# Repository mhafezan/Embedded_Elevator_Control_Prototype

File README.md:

# Embedded Elevator Control Prototype

A C-based embedded elevator controller prototype that simulates the core logic of a multi-floor elevator system using a finite-state machine. The project includes both a terminal-based simulator and a graphical simulator built with raylib.

This project demonstrates embedded control concepts such as state-machine design, safety input handling, request queue management, motor control logic, and separation between controller firmware logic and user-interface visualization.

---

## Project Overview

The system models a simplified elevator controller for a 10-floor building. The controller processes cabin requests, hall requests, door obstruction signals, emergency stop input, and upper/lower limit switch conditions. Based on these inputs, it updates the elevator state, motor command, current floor, target floor, door status, and pending request queue.

The project is structured to resemble the type of control logic that could run periodically on a microcontroller after reading GPIO or sensor inputs.

---

## Key Features

- Finite-state machine-based elevator control logic
- Supports 10 floors by default
- Cabin floor requests
- Hall UP and Hall DOWN requests
- FIFO request queue
- Duplicate request prevention
- Emergency stop handling with highest priority
- Door obstruction handling
- Upper and lower limit switch protection
- Terminal-based simulation
- Professional GUI simulation using raylib
- Modular separation between controller logic and visualization

---

## Elevator States

The controller supports the following operating states:

| State | Description |
|---|---|
| `STATE_IDLE` | Elevator is stopped and waiting for a valid request |
| `STATE_MOVING_UP` | Elevator is moving upward toward the target floor |
| `STATE_MOVING_DOWN` | Elevator is moving downward toward the target floor |
| `STATE_DOOR_OPEN` | Elevator has arrived and the door is open |
| `STATE_EMERGENCY_STOP` | Emergency stop is active and motor movement is disabled |

---

## Motor Commands

The motor output is represented using three commands:

| Motor Command | Description |
|---|---|
| `MOTOR_STOP` | Motor is stopped |
| `MOTOR_UP` | Motor moves the elevator upward |
| `MOTOR_DOWN` | Motor moves the elevator downward |

---

## Safety Inputs

The controller supports the following safety-related inputs:

| Input | Description |
|---|---|
| `emergency_stop` | Immediately stops the elevator and enters emergency mode |
| `door_obstruction` | Keeps the door open while an obstruction is detected |
| `upper_limit_switch` | Prevents upward movement beyond the upper limit |
| `lower_limit_switch` | Prevents downward movement beyond the lower limit |

---

## Project Structure

```text
.
├── elevator_controller.c    # Core elevator controller logic
├── elevator_controller.h    # Controller states, data structures, and function declarations
├── main.c                   # Terminal-based elevator simulator
├── gui_simulator.c          # Graphical elevator simulator using raylib
├── stm32_main.c             # STM32 firmware entry-point scaffold
├── stm32_gpio_config.h      # STM32 pin mapping and GPIO configuration API
├── stm32_gpio_config.c      # STM32 GPIO debounce, input, and safe output layer
├── STM32_HARDWARE_PORTING.md # STM32 hardware integration checklist
└── README.md                # Project documentation
```

---

## Core Controller Design

The controller is implemented as a modular firmware-style component. The main API functions are:

```c
void Elevator_Init(ElevatorController *controller);
void Elevator_Update(ElevatorController *controller, ElevatorInputs inputs);
void Elevator_PrintStatus(const ElevatorController *controller);
```

### `Elevator_Init`

Initializes the elevator controller to a safe default condition:

- Current floor: 1
- Target floor: 1
- State: `STATE_IDLE`
- Motor: `MOTOR_STOP`
- Door: closed
- Request queue: empty

### `Elevator_Update`

Executes one controller update cycle. This function processes all input signals, updates the request queue, applies safety logic, and advances the finite-state machine.

In the simulation, each update cycle moves the elevator by one floor when the motor is active.

### `Elevator_PrintStatus`

Prints the current elevator status, including:

- Current floor
- Target floor
- Controller state
- Motor command
- Door status

---

## Request Queue Logic

The controller uses a FIFO request queue to store pending floor requests. Requests are accepted from:

- Cabin request buttons
- Hall UP request buttons
- Hall DOWN request buttons

The queue logic includes:

- Floor range validation
- Queue capacity checking
- Duplicate request prevention
- Automatic removal of served requests

---

## Terminal Simulation

The terminal simulator allows users to manually enter elevator requests and safety inputs.

### Compile Terminal Version

```bash
gcc -g main.c elevator_controller.c -o elevator_controller.exe
```

### Run Terminal Version

```bash
./elevator_controller.exe
```

On Windows Command Prompt or PowerShell, you can also run:

```bash
elevator_controller.exe
```

### Terminal Inputs

During execution, the program asks for:

- Cabin request floor
- Hall UP request floor
- Hall DOWN request floor
- Door obstruction status
- Emergency stop status
- Upper limit switch status
- Lower limit switch status

Enter `0` when there is no floor request.

---

## GUI Simulation

The GUI simulator provides a visual dashboard for the elevator system. It displays the elevator shaft, current floor, target floor, controller state, motor command, door status, and safety inputs.

The GUI is implemented using raylib and keeps the embedded controller logic separated from the visualization layer.

### GUI Features

- Visual elevator shaft
- Current floor indicator
- Target floor highlight
- Cabin movement visualization
- Floor request buttons
- Emergency stop button
- Door obstruction toggle
- Upper limit switch toggle
- Lower limit switch toggle
- Live display of state, motor, and door status

---

## Requirements

### For Terminal Simulation

- GCC compiler
- C standard library

### For GUI Simulation

- GCC compiler
- raylib
- Windows/MSYS2 environment recommended for the provided build command

---

## Compile GUI Version on Windows/MSYS2

After installing raylib, compile the GUI simulator using:

```bash
gcc gui_simulator.c elevator_controller.c -o gui_simulator.exe -lraylib -lopengl32 -lgdi32 -lwinmm
```

### Run GUI Version

```bash
./gui_simulator.exe
```

Or on Windows:

```bash
gui_simulator.exe
```

---

## Example Usage

### Terminal Simulation Example

```text
Embedded Elevator Controller Simulation Started
Valid floors: 1 to 10

Cabin request floor 1 to 10, or 0 for no cabin request: 5
Hall UP request floor 1 to 10, or 0 for no hall UP request: 0
Hall DOWN request floor 1 to 10, or 0 for no hall DOWN request: 0
Door obstruction? 1=yes, 0=no: 0
Emergency stop? 1=yes, 0=no: 0
Upper limit switch active? 1=yes, 0=no: 0
Lower limit switch active? 1=yes, 0=no: 0
```

The controller then updates its state and moves the elevator toward the requested floor.

---

## Design Highlights

### 1. Modular Firmware-Style Architecture

The controller logic is implemented independently from the terminal and GUI interfaces. This makes the project easier to test, extend, and port to embedded hardware.

### 2. Finite-State Machine Control

The elevator behavior is modeled using explicit operating states. This improves readability and makes the controller behavior predictable.

### 3. Safety-First Logic

Emergency stop has the highest priority and immediately disables motor movement. Limit switches prevent movement beyond valid floor boundaries, and door obstruction keeps the door open.

### 4. GUI and Logic Separation

The GUI simulator only sends user input events to the controller. It does not directly modify the control behavior, which preserves the separation between application logic and visualization.

---

## STM32 Hardware Firmware

The repository includes an STM32-oriented firmware scaffold that connects the shared elevator controller to GPIO inputs and outputs. The STM32 layer now separates board-specific GPIO configuration into `stm32_gpio_config.h` and `stm32_gpio_config.c`, debounces inputs, uses active-low pull-up button logic, supports optional floor-position sensors, and applies safe motor-output interlocking before driving motor direction pins.

This firmware must still be imported into a STM32CubeIDE project generated for the exact target MCU and board. Before flashing real hardware, replace the example clock configuration with the CubeMX-generated `SystemClock_Config`, verify every pin against the schematic, use external motor/door driver hardware, and wire emergency stop and final limit switches into a hardware safety path. See `01_mcu_elevator_control_firmware/STM32_HARDWARE_PORTING.md` for the full checklist.

---

## Possible Future Improvements

- Add direction-aware request scheduling
- Add separate cabin and hall request indicators
- Add door opening and closing timers
- Add acceleration and deceleration profiles
- Add support for multiple elevators
- Add unit tests for controller states and edge cases
- Add hardware abstraction layer for GPIO-based deployment
- Port the controller logic to an embedded board such as STM32, Arduino, or Raspberry Pi Pico

---

## Technologies Used

- C programming language
- GCC compiler
- raylib graphics library
- Finite-state machine design
- Embedded control logic concepts

---

## Learning Objectives

This project is useful for practicing:

- Embedded C programming
- State-machine implementation
- Real-time control logic
- Safety-critical input handling
- Modular software design
- GUI-based simulation of embedded systems
- Separating firmware logic from visualization logic

---

## Author

Mohammad Hafezan

---

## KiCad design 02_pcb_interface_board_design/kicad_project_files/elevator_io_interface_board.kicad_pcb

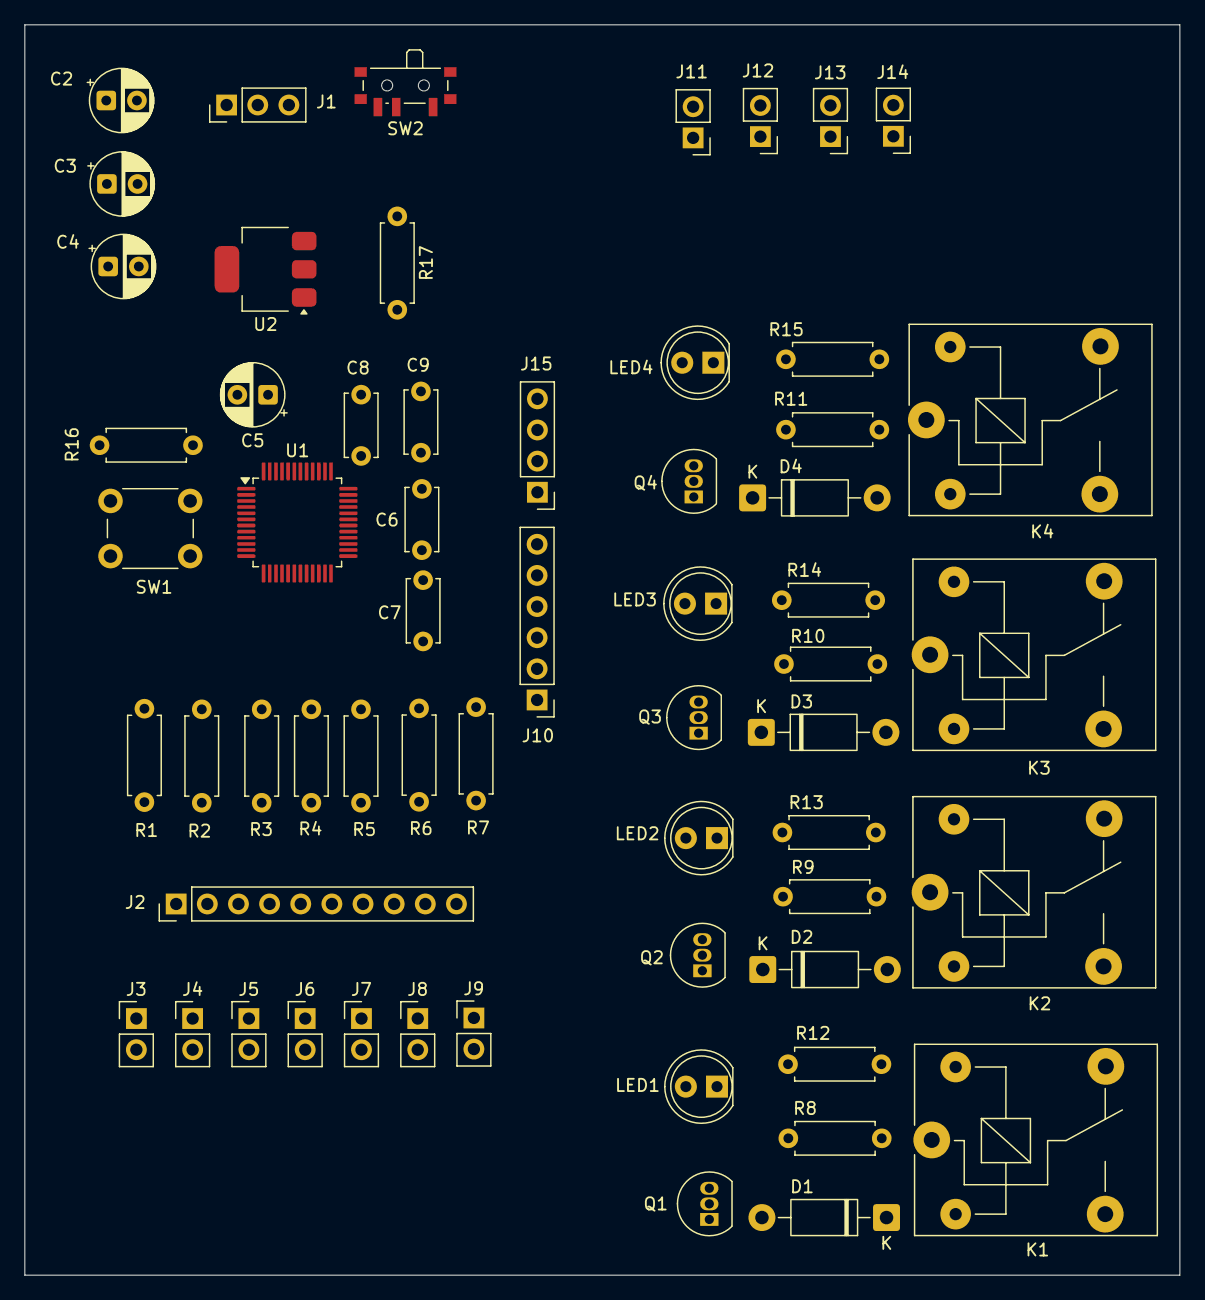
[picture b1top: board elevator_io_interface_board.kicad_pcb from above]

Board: 2 copper layers, 94.2 x 102.0 mm, 60 parts (0 on the bottom side), 32 nets, no tracks yet.

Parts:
C2, C3, C4, C5: 10uF; CP_Radial_D5.0mm_P2.50mm
C6, C7, C8, C9: 100nF; C_Disc_D5.0mm_W2.5mm_P5.00mm
D1, D2, D3, D4: 1N4007; D_DO-41_SOD81_P10.16mm_Horizontal
J1: Power Input; PinHeader_1x03_P2.54mm_Vertical
J2: MCU Input Header; PinHeader_1x10_P2.54mm_Vertical
J3: Floor 1 Button; PinHeader_1x02_P2.54mm_Vertical
J4: Floor 2 Button; PinHeader_1x02_P2.54mm_Vertical
J5: Floor 3 Button; PinHeader_1x02_P2.54mm_Vertical
J6: Door Sensor; PinHeader_1x02_P2.54mm_Vertical
J7: Emergency Stop; PinHeader_1x02_P2.54mm_Vertical
J8: Upper Limit Switch; PinHeader_1x02_P2.54mm_Vertical
J9: Lower Limit Switch; PinHeader_1x02_P2.54mm_Vertical
J10: MCU Output Header; PinHeader_1x06_P2.54mm_Vertical
J11: Motor UP Output; PinHeader_1x02_P2.54mm_Vertical
J12: Motor DOWN Output; PinHeader_1x02_P2.54mm_Vertical
J13: Door OPEN Output; PinHeader_1x02_P2.54mm_Vertical
J14: Door CLOSE Output; PinHeader_1x02_P2.54mm_Vertical
J15: SWD_IO; PinHeader_1x04_P2.54mm_Vertical
K1, K2, K3, K4: Relay_SPDT; Relay_SPDT_SANYOU_SRD_Series_Form_C
LED1, LED2, LED3, LED4: Status_LED; LED_D5.0mm
Q1, Q2, Q3, Q4: 2N2222; TO-92_Inline
R1, R2, R3, R4, R5, R6, R7, R16, R17: 10k; R_Axial_DIN0207_L6.3mm_D2.5mm_P7.62mm_Horizontal
R8, R9, R10, R11: 1k; R_Axial_DIN0207_L6.3mm_D2.5mm_P7.62mm_Horizontal
R12, R13, R14, R15: 330; R_Axial_DIN0207_L6.3mm_D2.5mm_P7.62mm_Horizontal
SW1: SW_Push; SW_PUSH_6mm
SW2: SW_SPDT; SW_SPDT_PCM12
U1: STM32F103C8T6; LQFP-48_7x7mm_P0.5mm
U2: AMS1117-3.3; SOT-223-3_TabPin2

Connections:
+3.3V: C4.1, C5.1, C6.2, C7.2, C8.2, C9.2, J2.1, J3.1, J4.1, J5.1, J6.1, J7.1, J8.1, J9.1, J10.5, J15.1, R16.1, SW2.3 (C), U1.1 (VBAT), U1.24 (VDD), U1.36 (VDD), U1.48 (VDD), U2.2 (VO)
+5V: C3.1, J1.2, U2.3 (VI)
+12V: C2.1, D1.1 (K), D2.1 (K), D3.1 (K), D4.1 (K), J1.1
/DOOR_CLOSE_CMD: J10.4, R11.2, R15.2, U1.39 (PB3)
/DOOR_OBSTRUCTION: J2.6, J6.2, R4.2, U1.13 (PA3)
/DOOR_OPEN_CMD: J10.3, R10.2, R14.2, U1.20 (PB2)
/EMERGENCY_STOP: J2.7, J7.2, R5.2, U1.14 (PA4)
/FLOOR_1_REQ: J2.3, J3.2, R1.2, U1.10 (PA0)
/FLOOR_2_REQ: J2.4, J4.2, R2.2, U1.11 (PA1)
/FLOOR_3_REQ: J2.5, J5.2, R3.2, U1.12 (PA2)
/LIMIT_DOWN: J2.9, J9.2, R7.2, U1.16 (PA6)
/LIMIT_UP: J2.8, J8.2, R6.2, U1.15 (PA5)
/MOTOR_DOWN_CMD: J10.2, R9.2, R13.2, U1.19 (PB1)
/MOTOR_UP_CMD: J10.1, R8.2, R12.2, U1.18 (PB0)
/SWCLK: J15.3, U1.37 (PA14)
/SWDIO: J15.2, U1.34 (PA13)
GND: C2.2, C3.2, C4.2, C5.2, C6.1, C7.1, C8.1, C9.1, J1.3, J2.2, J10.6, J11.2, J12.2, J13.2, J14.2, J15.4, LED1.1 (K), LED2.1 (K), LED3.1 (K), LED4.1 (K), Q1.3 (E), Q2.3 (E), Q3.3 (E), Q4.3 (E), R1.1, R2.1, R3.1, R4.1, R5.1, R6.1, R7.1, SW1.1, SW2.1 (A), U1.8 (VSSA), U1.23 (VSS), U1.35 (VSS), U1.47 (VSS), U2.1 (GND)
unnamed: D1.2 (A), Q1.2 (C)
unnamed: D2.2 (A), Q2.2 (C)
unnamed: D3.2 (A), Q3.2 (C)
unnamed: D4.2 (A), Q4.2 (C)
unnamed: LED1.2 (A), R12.1
unnamed: LED2.2 (A), R13.1
unnamed: LED3.2 (A), R14.1
unnamed: LED4.2 (A), R15.1
unnamed: Q1.1 (B), R8.1
unnamed: Q2.1 (B), R9.1
unnamed: Q3.1 (B), R10.1
unnamed: Q4.1 (B), R11.1
unnamed: R17.1, SW2.2 (B)
unnamed: R17.2, U1.44 (BOOT0)
unnamed: R16.2, SW1.2, U1.7 (NRST)

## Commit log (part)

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2026-05-01 Add initial README with update notice
2026-05-01 MCU Elevator Contro Firmware added!
2026-05-01 MCU elevator controller firmware finalized!
2026-05-04 "Separate cabin and hall call request inputs Added"
2026-05-05 MCU elevator control firmware finalized!
2026-05-12 PCB Design Added for SMT32!
2026-05-21 PCB Finalize!
2026-05-21 PCB Design finalized!
2026-05-29 Add STM32 firmware with GPIO-based input reading and motor control outputs
2026-05-29 Add GPIO configuration header for easy pin management
2026-05-29 Add button debouncing header for robust input handling
2026-05-29 PCB updated!
2026-05-29 Latest update!
2026-05-29 Harden STM32 elevator firmware scaffold
